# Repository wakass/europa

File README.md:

A single PCB eurorack module which doubles as its own front-panel and has an FPGA powering it. 

### Notes
For now it is based on the UPduino formfactor, but considering the feather formfactor.

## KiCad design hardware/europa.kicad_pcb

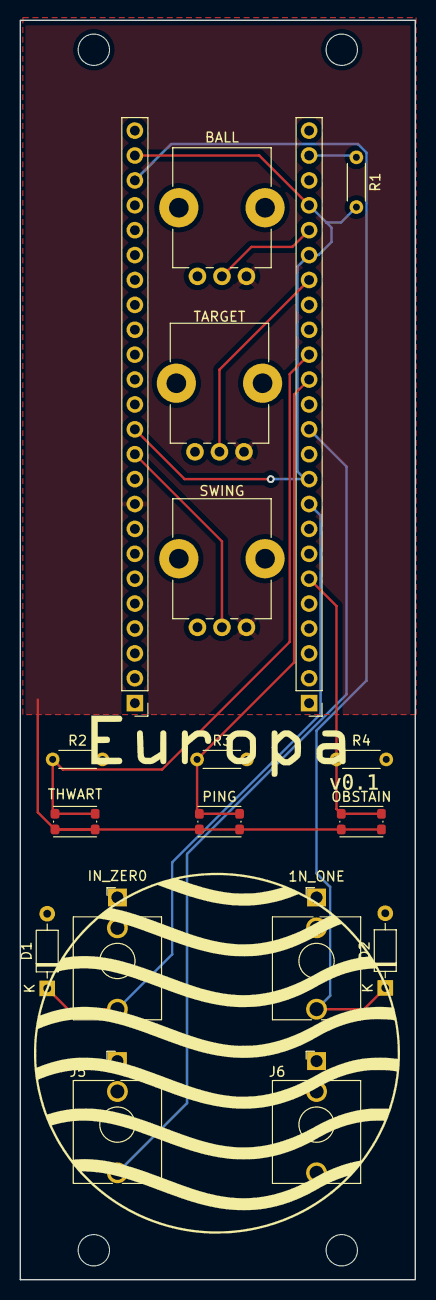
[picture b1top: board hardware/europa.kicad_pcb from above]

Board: 2 copper layers, 40.3 x 128.5 mm, 19 parts (0 on the bottom side), 13 nets.

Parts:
1N_ONE: AudioJack2_Ground; Jack_3.5mm_QingPu_WQP-PJ398SM_Vertical_CircularHoles
BALL: 5k; Potentiometer_Alps_RK09K_Single_Vertical
D1, D2: 3.3V; D_DO-35_SOD27_P7.62mm_Horizontal
IN_ZER0: AudioJack2; Jack_3.5mm_QingPu_WQP-PJ398SM_Vertical_CircularHoles
J1: Left; PinHeader_1x24_P2.54mm_Vertical
J2: Right; PinHeader_1x24_P2.54mm_Vertical
J5, J6: AudioJack2_Ground; Jack_3.5mm_QingPu_WQP-PJ398SM_Vertical_CircularHoles
OBSTAIN: KMR2; SW_Push_KMR2
PING: KMR2; SW_Push_KMR2
R1: 1K; R_Axial_DIN0204_L3.6mm_D1.6mm_P5.08mm_Horizontal
R2, R3, R4: 12k; R_Axial_DIN0204_L3.6mm_D1.6mm_P5.08mm_Horizontal
Ref**: Val**; Europe_Graphics
SWING: 5k; Potentiometer_Alps_RK09K_Single_Vertical
TARGET: 5k; Potentiometer_Alps_RK09K_Single_Vertical
THWART: KMR2; SW_Push_KMR2

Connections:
+3V3: BALL.1, J2.9, OBSTAIN.2, PING.2, SWING.1, TARGET.1, THWART.2
A0: BALL.2, J1.20
A1: J1.18, TARGET.2
A2: J2.11, SWING.2
AU_IN0: D1.1 (K), IN_ZER0.T, J1.9
AU_IN1: 1N_ONE.T, D2.1 (K), J2.22
AU_OUT0: J1.12, J5.T
BUTTON0: J1.15, R2.1, THWART.1
BUTTON1: J1.14, PING.1, R3.1
BUTTON2: J1.6, OBSTAIN.1, R4.1
GND: 1N_ONE.S, BALL.3, D1.2 (A), D2.2 (A), IN_ZER0.S, J1.7, J2.1, J2.10, J5.S, J6.S, R2.2, R3.2, R4.2, SWING.3, TARGET.3
REF_CLK: J1.23, R1.1
VREF: J1.10, J1.19, J1.21, J2.12, J2.23, R1.2

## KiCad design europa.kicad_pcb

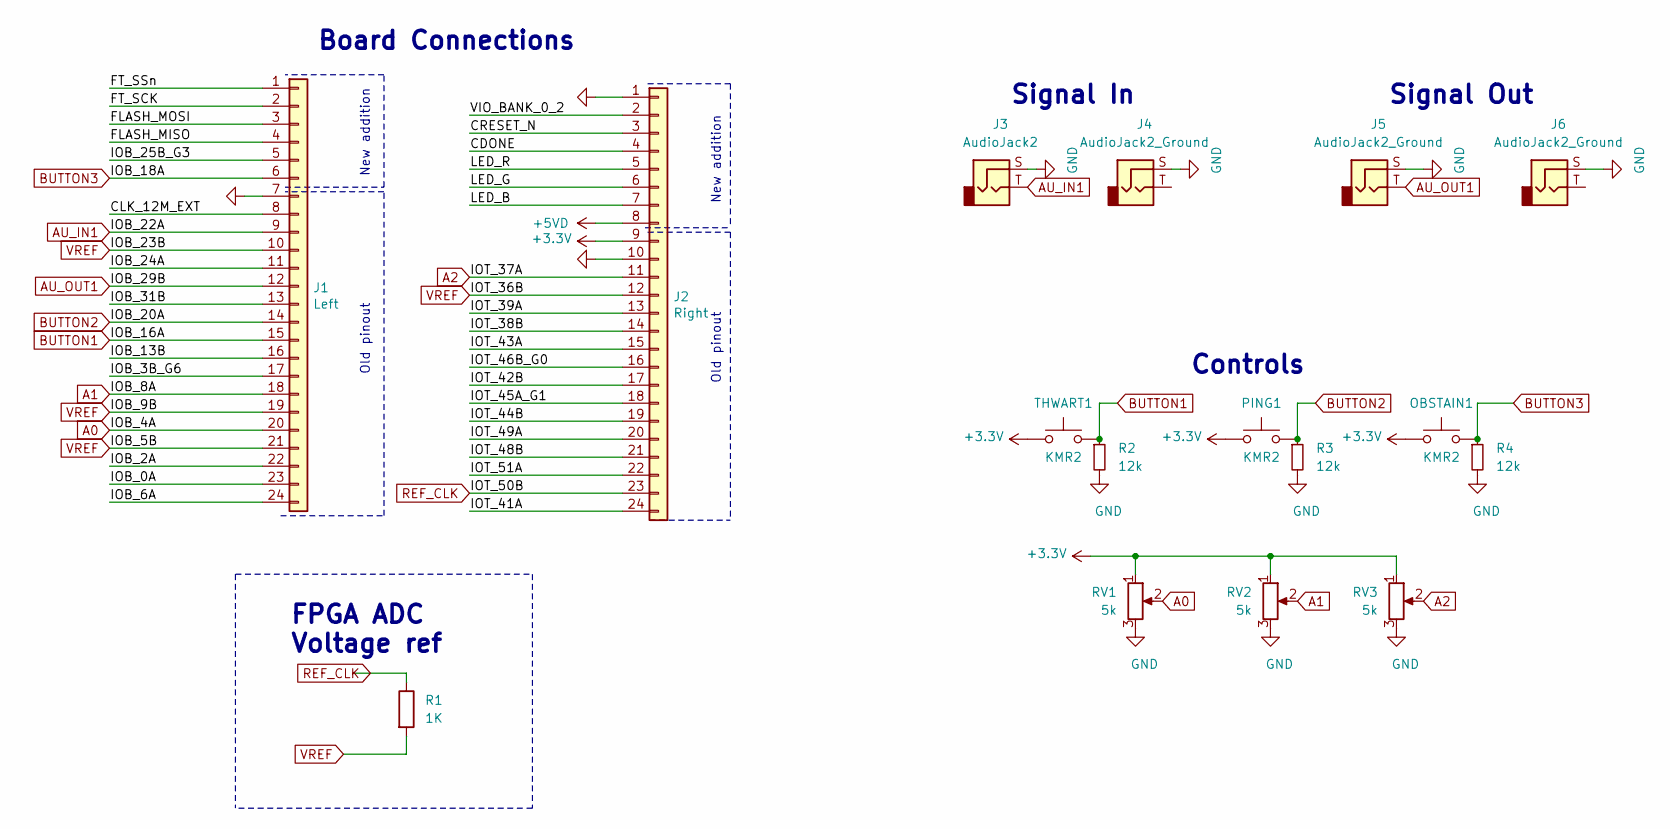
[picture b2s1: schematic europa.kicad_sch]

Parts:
J1: Left; PinHeader_1x24_P2.54mm_Vertical
J2: Right; PinHeader_1x24_P2.54mm_Vertical
J3: AudioJack2; Jack_3.5mm_QingPu_WQP-PJ398SM_Vertical_CircularHoles
J4, J5, J6: AudioJack2_Ground; Jack_3.5mm_QingPu_WQP-PJ398SM_Vertical_CircularHoles
OBSTAIN1: KMR2; SW_Push_KMR2; MPN KMR221GLFS; LCSC C72443
PING1: KMR2; SW_Push_KMR2; MPN KMR221GLFS; LCSC C72443
R1: 1K; R_Axial_DIN0204_L3.6mm_D1.6mm_P5.08mm_Horizontal
R2, R3, R4: 12k; R_Axial_DIN0204_L3.6mm_D1.6mm_P5.08mm_Horizontal
RV1, RV2, RV3: 5k; Potentiometer_Alps_RK09K_Single_Vertical
THWART1: KMR2; SW_Push_KMR2; MPN KMR221GLFS; LCSC C72443

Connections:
+3V3: J2.9, OBSTAIN1.2, PING1.2, RV1.1, RV2.1, RV3.1, THWART1.2
+5VD: J2.8
/CDONE: J2.4
/CLK_12M_EXT: J1.8
/CRESET_N: J2.3
/FLASH_MISO: J1.4
/FLASH_MOSI: J1.3
/FT_SCK: J1.2
/FT_SSn: J1.1
/IOB_0A: J1.23
/IOB_2A: J1.22
/IOB_3B_G6: J1.17
/IOB_6A: J1.24
/IOB_13B: J1.16
/IOB_24A: J1.11
/IOB_25B_G3: J1.5
/IOB_31B: J1.13
/IOT_38B: J2.14
/IOT_39A: J2.13
/IOT_41A: J2.24
/IOT_42B: J2.17
/IOT_43A: J2.15
/IOT_44B: J2.19
/IOT_45A_G1: J2.18
/IOT_46B_G0: J2.16
/IOT_48B: J2.21
/IOT_49A: J2.20
/IOT_51A: J2.22
/LED_B: J2.7
/LED_G: J2.6
/LED_R: J2.5
/VIO_BANK_0_2: J2.2
A0: J1.20, RV1.2
A1: J1.18, RV2.2
A2: J2.11, RV3.2
AU_IN1: J1.9, J3.T
AU_OUT1: J1.12, J5.T
BUTTON1: J1.15, R2.1, THWART1.1
BUTTON2: J1.14, PING1.1, R3.1
BUTTON3: J1.6, OBSTAIN1.1, R4.1
GND: J1.7, J2.1, J2.10, J3.S, J4.S, J5.S, J6.S, R2.2, R3.2, R4.2, RV1.3, RV2.3, RV3.3
REF_CLK: J2.23, R1.1
VREF: J1.10, J1.19, J1.21, J2.12, R1.2

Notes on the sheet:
FPGA ADC Voltage ref
Board Connections
New addition
Old pinout
Signal In
Controls
Signal Out

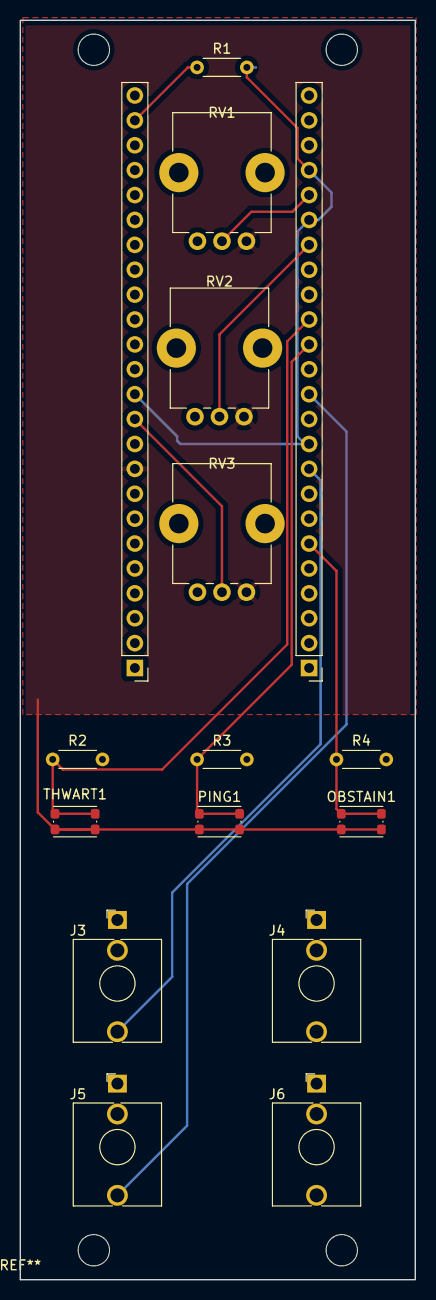
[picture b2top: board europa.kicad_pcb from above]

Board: 2 copper layers, 40.3 x 128.5 mm, 16 parts (0 on the bottom side), 12 nets.

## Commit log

2021-03-07 Added readme
2021-03-07 Layout finished, needs tweak in proper components
2021-03-07 Mono plugs now connecting properly. Switches found at farnell
2021-03-08 Europa 0.1, gerber files send to jlpcb. Added RTL reference design for adc.
2021-03-14 First two modules of adc/tdc translated to verilog.
2021-03-14 Added a top file for proper compilation? XD
2021-03-14 Added more modules
2021-03-14 Dummy drivers for compilation
2021-03-14 Fixed first FPGA bug! Generate for-loop off-by one error :S
2021-03-14 Added testbench for fine_tdc
2021-03-15 Added count_ones, therm2bin, some showrtl code for yosys.
2021-03-15 Fixed concatenation oversight when translating vhdl to verilog
2021-03-15 Fixed another vhdl-related contatenation mistake, added therm2bin testbench
2021-03-17 Started implementation top module
2021-03-17 Compilation of top, with manually constrained ports. Temporary. Changes to clock manager
2021-03-17 Added default width for dig out
2021-03-18 Added SConstruct file and SIMULATION define for simulation
2021-03-28 Fixed bugs in adcv (xilinx primitive translation errors). Added more testing code. More prelim testing on real hardware. Clock manager changes.
2021-03-31 Changed to more sane delay line parameters for up5k. Making sure SBCARRY isnt optimized away with keep statements. Still feels hacky :/
2021-03-31 Added test-cases
2021-03-31 Added toolchain instruction
2021-03-31 Small mod
2021-04-15 Started the simple units. Simple explorational demonstration units
2021-04-15 Additional documentation, small changes here and there
2021-04-16 First working simple unit for comparator. (Tentative) Small changes to deltasigma
2021-04-16 Hacked SB_IO to stop using the clock for the comparator
2021-05-06 Sanitized hardware layout numbering, some silkscreen mods
2021-05-06 Upduino/europe hardware pinouts, streamlined to simple units
2021-05-06 Fixed up simple units to use 'new' nomenclature of europa
2021-05-11 Added verifla logic analyzer to project, with demo project comparator_instrumented. Changes to files to reflect naming scheme changes
2021-05-22 Added zener diode series resistor for 5V TTL
